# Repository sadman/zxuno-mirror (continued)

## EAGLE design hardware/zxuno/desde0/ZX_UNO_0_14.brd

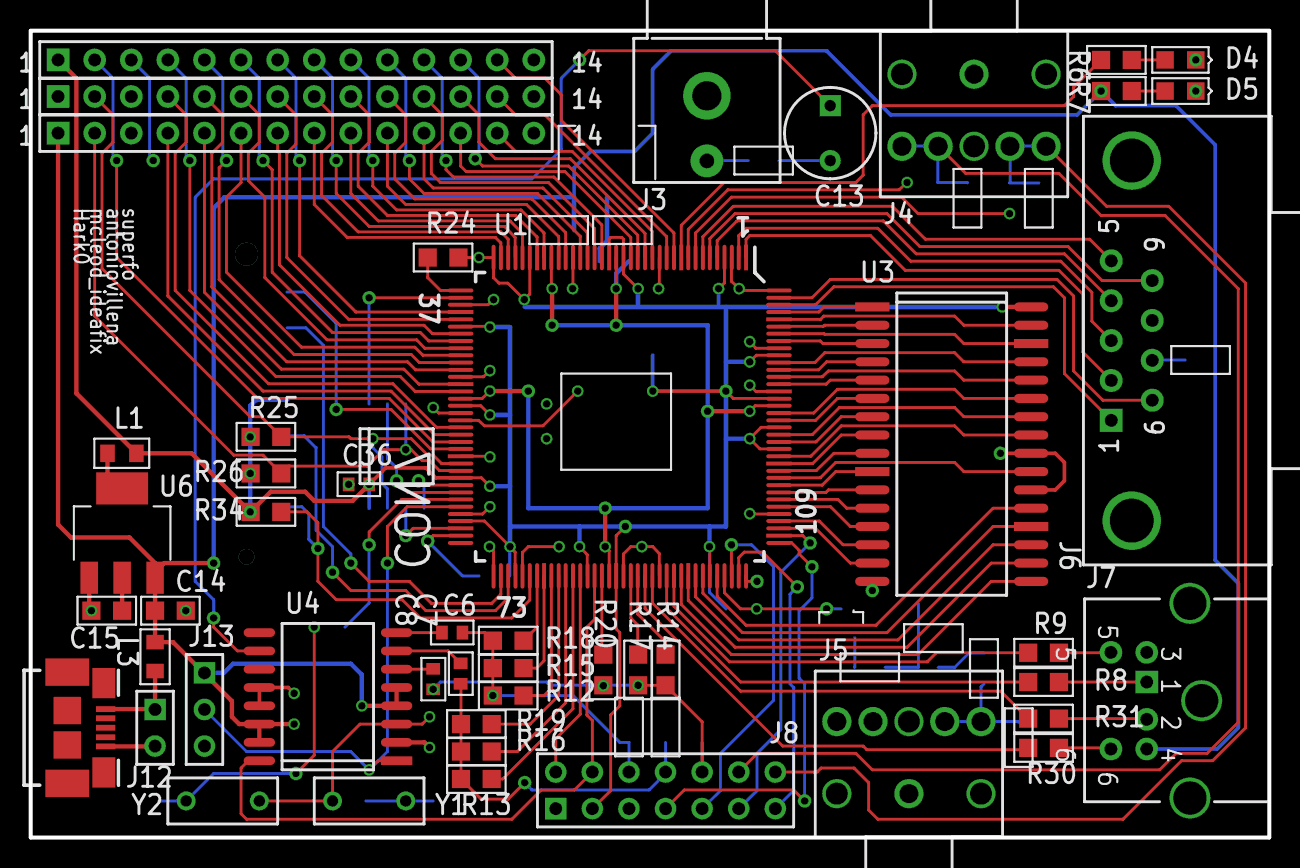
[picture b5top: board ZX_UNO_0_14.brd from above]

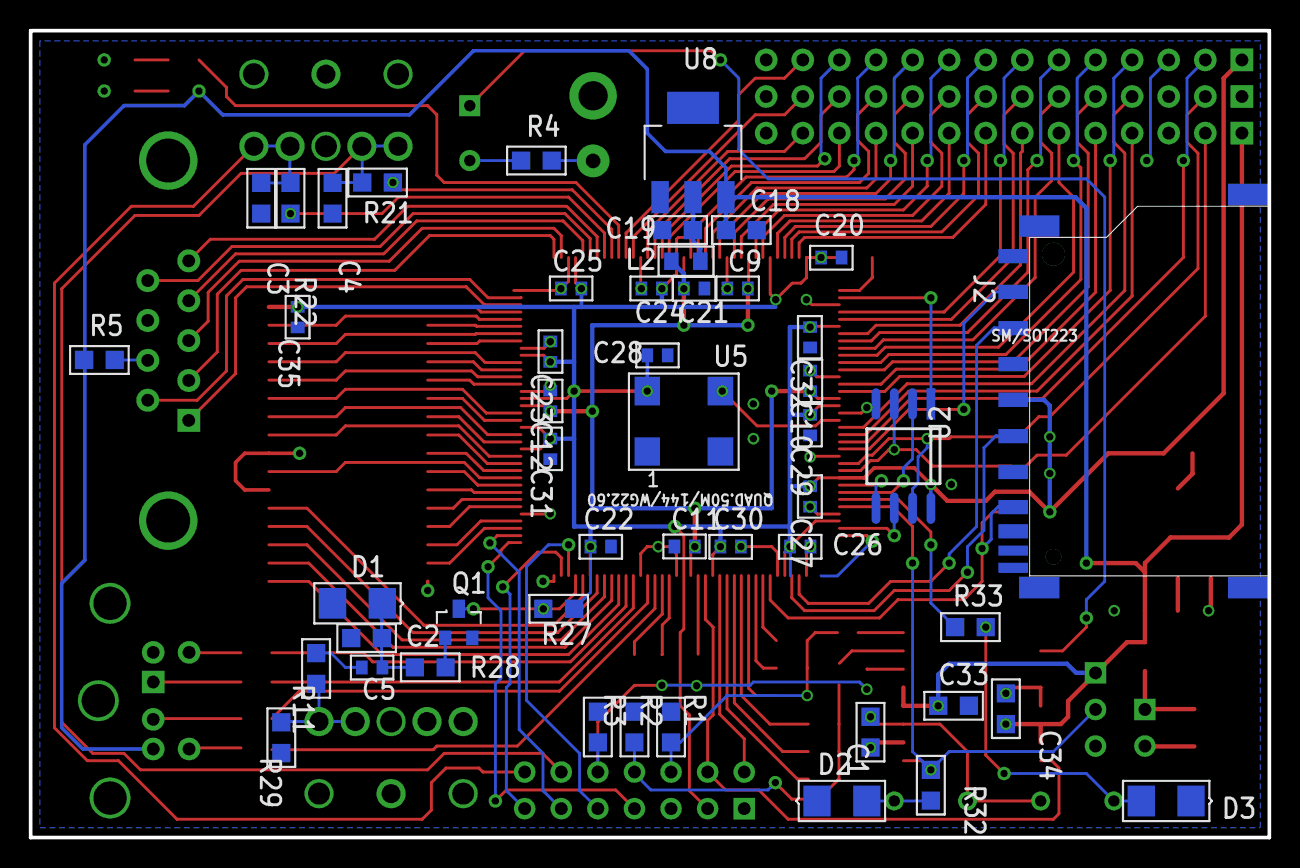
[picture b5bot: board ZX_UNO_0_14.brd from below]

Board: 2 copper layers, 86.0 x 56.0 mm, 97 parts (49 on the bottom side), 135 nets.

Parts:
C1: 10pF; SM/C_0805_3PRIMARY
C2, C3, C4: 10nF; SM/C_0805_2PRIMARY
C5, C8, C9, C10, C11, C12, C20, C21, C22, C23, C24, C25, C26, C27, C28, C29, C30, C31, C32, C35, C36: 100nF; SM/C_0603_1PRIMARY
C6, C7: 100nF; SM/C_0603_2PRIMARY
C13: 220uF; CYL/D.250/LS.150/.031_1PRIMARY
C14, C15: 4.7uF; SM/C_0805_1PRIMARY
C18, C19: 4.7uF; SM/C_0805_2PRIMARY
C33, C34: 10uF; SM/C_0805_1PRIMARY
D1, D2, D3: 1N4148; SM/DO213AA_21_1PRIMARY
D4, D5: LED; SM/D_0805_21_1PRIMARY
J1: microUSB; MICRO_USB_609-4613-1-ND_1PRIMARY
J2: SD; SD_101-00708-64-ND_1PRIMARY
J3: RCA; RCA_JACK_RCJ-04X_1PRIMARY
J4: Audio; AUDIO_JACK_STX-3120_1PRIMARY
J5: EAR; AUDIO_JACK_STX-3120_1PRIMARY
J6: JOYSTICK; DSUB/RP.318/TM/9_1PRIMARY
J7: KEYBOARD; DINC/MIN_TM/6_1PRIMARY
J8: Header_7X2; HDR2X7_1PRIMARY
J9, J10, J11: HEADER_14; BLKCON.100/VH/TM1SQ/W.100/14_1PRIMARY
J12: Header_2; HDR1X2_1PRIMARY
J13: Header_3; HDR1X3_1PRIMARY
L1, L2, L3: Inductor; SM/L_0805_1PRIMARY
Q1: BC846; SM/SOT23_231_1PRIMARY
R1, R2, R4: 75; SM/R_0805_2PRIMARY
R3: 75; SM/R_0805_5PRIMARY
R5: 300; SM/R_0805_2PRIMARY
R6: 300; SM/R_0805_1PRIMARY
R7: 300; SM/R_0805_3PRIMARY
R8, R9: 270; SM/R_0805_4PRIMARY
R11: 470; SM/R_0805_2PRIMARY
R12, R13: 470; SM/R_0805_1PRIMARY
R14: 470; SM/R_0805_4PRIMARY
R15, R16, R17: 1K; SM/R_0805_4PRIMARY
R18, R19: 2K; SM/R_0805_4PRIMARY
R20, R25, R26: 2K; SM/R_0805_1PRIMARY
R21, R22: 3K9; SM/R_0805_1PRIMARY
R24: 4K7; SM/R_0805_3PRIMARY
R27, R32, R33, R34: 10K; SM/R_0805_1PRIMARY
R28, R29: 10K; SM/R_0805_2PRIMARY
R30, R31: 270; SM/R_0805_1PRIMARY
U1: XC6SLX9/TFP144_1; QUAD.50M/144/WG22.60_1PRIMARY
U2: W25X40BV/W25Q80BV; SOJ.050/8/WB.300/L.200_1PRIMARY
U3: CY62148EV30; SOG.050/32/WG.480/L.825_1PRIMARY
U4: AD724; SOJ.050/16/WB.400/L.400_1PRIMARY
U5: 50MHz; SM/OSC_1PRIMARY
U6: ZLDO1117G33TA; SM/SOT223_2PRIMARY
U8: ZLDO1117G12TA; SM/SOT223_1PRIMARY
Y1: 3.58M; RAD/.300X.125/LS.200/.031_1PRIMARY
Y2: 4.43M; RAD/.300X.125/LS.200/.031_1PRIMARY

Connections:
1.2V: C9.1, C10.1, C11.1, C12.1, C21.1, L2.2, U1.19, U1.28, U1.52, U1.89, U1.128
3.3V: C20.1, C22.1, C23.1, C24.1, C25.1, C26.1, C27.1, C28.1, C29.1, C30.1, C31.1, C32.1, C35.1, C36.1, J2.4, J8.3, J11.1, L1.2, R24.2, R25.2, R26.2, R27.1, R34.2, U1.4, U1.18, U1.20, U1.31, U1.36, U1.42, U1.53, U1.63, U1.69, U1.76, U1.86, U1.90, U1.103, U1.122, U1.125, U1.129, U1.135, U2.8, U3.32, U5.4
5V: C14.1, C18.1, C33.1, C34.1, J7.4, J9.1, J13.1, L3.2, R5.2, R7.1, U4.4, U4.5, U4.14, U4.15, U6.3, U8.3
B: C6.1, J8.6, R1.1, R12.2, R15.2, R18.2
B0: R18.1, U1.79
B1: R15.1, U1.80
B2: R12.1, U1.81
CLK: U1.55, U5.3
CSYNC: J8.4, U1.87, U4.16
EAR: Q1.1, R27.2, U1.105
EXT1_WP_: J9.2, R26.1, U1.62, U2.3
EXT2_HOLD_: J10.2, R25.1, U1.61, U2.7
EXT3: J11.2, U1.58
EXT7: J9.4, U1.57
EXT8: J10.4, U1.56
EXT9: J11.4, U1.51
EXT10: J9.5, U1.50
EXT11: J10.5, U1.48
EXT12: J11.5, U1.47
EXT13: J9.6, U1.46
EXT14: J10.6, U1.45
EXT15: J11.6, U1.44
EXT16: J9.7, U1.43
EXT17: J10.7, U1.41
EXT18: J11.7, U1.40
EXT19: J9.8, U1.35
EXT20: J10.8, U1.34
EXT21: J11.8, U1.33
EXT22: J9.9, U1.32
EXT23: J10.9, U1.30
EXT24: J11.9, U1.29
EXT25: J9.10, U1.27
EXT26: J10.10, U1.26
EXT27: J11.10, U1.24
EXT28: J9.11, U1.23
EXT29: J10.11, U1.22
EXT30: J11.11, U1.21
EXT31: J9.12, U1.17
EXT32: J11.12, U1.16
EXT33: J10.12, U1.15
EXT34: J9.13, U1.14
EXT35: J10.13, U1.12
EXT36: J11.13, U1.11
FLASH_CS: U1.38, U2.1
FLASH_MISO: U1.65, U2.2
FLASH_MOSI: U1.64, U2.5
FLASH_SCK: U1.70, U2.6
G: C7.1, J8.8, R2.1, R13.2, R16.2, R19.2
G0: R19.1, U1.82
G1: R16.1, U1.83
G2: R13.1, U1.84
GND: C1.2, C2.1, C3.1, C4.1, C9.2, C10.2, C11.2, C12.2, C14.2, C15.2, C18.2, C19.2, C20.2, C21.2, C22.2, C23.2, C24.2, C25.2, C26.2, C27.2, C28.2, C29.2, C30.2, C31.2, C32.2, C33.2, C34.2, C35.2, C36.2, D1.1, D2.2, D3.2, D4.2, D5.2, J1.5, J2.3, J2.6, J3.2, J4.1, J5.1, J6.8, J7.3, J7.7, J7.8, J7.9, J8.5, J9.14, J10.1, J10.14, J11.14, J12.2, J13.3, Q1.3, R1.2, R2.2, R3.2, R29.2, U1.3, U1.13, U1.25, U1.49, U1.54, U1.60, U1.68, U1.73, U1.77, U1.91, U1.96, U1.108, U1.113, U1.130, U1.136, U1.144, U2.4, U3.16, U3.22, U3.24, U4.2, U4.12, U4.13, U5.2, U6.1, U8.1
JOY1: J6.5, U1.7
JOY2: J6.4, U1.5
JOY3: J6.3, U1.2
JOY4: J6.2, U1.1
JOY5: J6.9, U1.6
JOY6: J6.1, U1.142
JOY7: J6.6, U1.143
L-OUT: C3.2, J4.2, J4.3, J8.14, R22.2
LED: R6.1, U1.10
LEFT: R22.1, U1.8
NETC1_1: C1.1, U4.3, Y1.1, Y2.1
NETC2_2: C2.2, C5.2, D1.2, R28.1
NETC5_1: C5.1, R11.2
NETC6_2: C6.2, U4.8
NETC7_2: C7.2, U4.7
NETC8_2: C8.2, U4.6
NETC13_1: C13.1, U4.10
NETC13_2: C13.2, R4.1
NETC15_1: C15.1, L1.1, U6.2, U6.4
NETC19_1: C19.1, L2.1, U8.2, U8.4
NETD2_1: D2.1, R32.2, Y1.2
NETD3_1: D3.1, R33.1, Y2.2
NETD4_1: D4.1, R6.2
NETD5_1: D5.1, R7.2
NETJ1_1: J1.1, J12.1, L3.1
NETJ3_1: J3.1, R4.2
NETJ5_4: J5.4, J5.5, R11.1, R29.1
NETJ6_7: J6.7, R5.1
NETJ7_1: J7.1, R8.1
NETJ7_2: J7.2, R31.1
NETJ7_5: J7.5, R9.1
NETJ7_6: J7.6, R30.1
NETQ1_2: Q1.2, R28.2
NETR24_1: R24.1, U1.37
PS2_CLK: R9.2, U1.98
PS2_DATA: R8.2, U1.97
PS2_PIN2: R31.2, U1.95
PS2_PIN6: R30.2, U1.94
R: C8.1, J8.10, R3.1, R14.2, R17.2, R20.2
R0: R20.1, U1.88
R1: R17.1, U1.92
R2: R14.1, U1.93
R-OUT: C4.2, J4.4, J4.5, J8.12, R21.2
RIGHT: R21.1, U1.9
SD_CS: J2.1, U1.59
SD_MISO: J2.7, R34.1, U1.78
SD_MOSI: J2.2, U1.74
SD_SCK: J2.5, U1.75
STDN: J13.2, R32.1, U1.67, U4.1
STDNB: R33.2, U1.66
TCK: J8.7, U1.109
TDI: J8.11, U1.110
TDO: J8.9, U1.106
TMS: J8.13, U1.107
VSYNC: J8.2, U1.85
WR: U1.134, U3.29
XA0: U1.115, U3.12
XA1: U1.116, U3.11
XA2: U1.117, U3.10
XA3: U1.119, U3.9
XA4: U1.120, U3.8
XA5: U1.123, U3.7
XA6: U1.126, U3.6
XA7: U1.131, U3.5
XA8: U1.127, U3.27
XA9: U1.124, U3.26
XA10: U1.118, U3.23
XA11: U1.121, U3.25
XA12: U1.133, U3.4
XA13: U1.132, U3.28
XA14: U1.137, U3.3
XA15: U1.140, U3.31
XA16: U1.139, U3.2
XA17: U1.141, U3.1
XA18: U1.138, U3.30
XD0: U1.114, U3.13
XD1: U1.112, U3.14
XD2: U1.111, U3.15
XD3: U1.99, U3.17
XD4: U1.100, U3.18
XD5: U1.101, U3.19
XD6: U1.102, U3.20
XD7: U1.104, U3.21
